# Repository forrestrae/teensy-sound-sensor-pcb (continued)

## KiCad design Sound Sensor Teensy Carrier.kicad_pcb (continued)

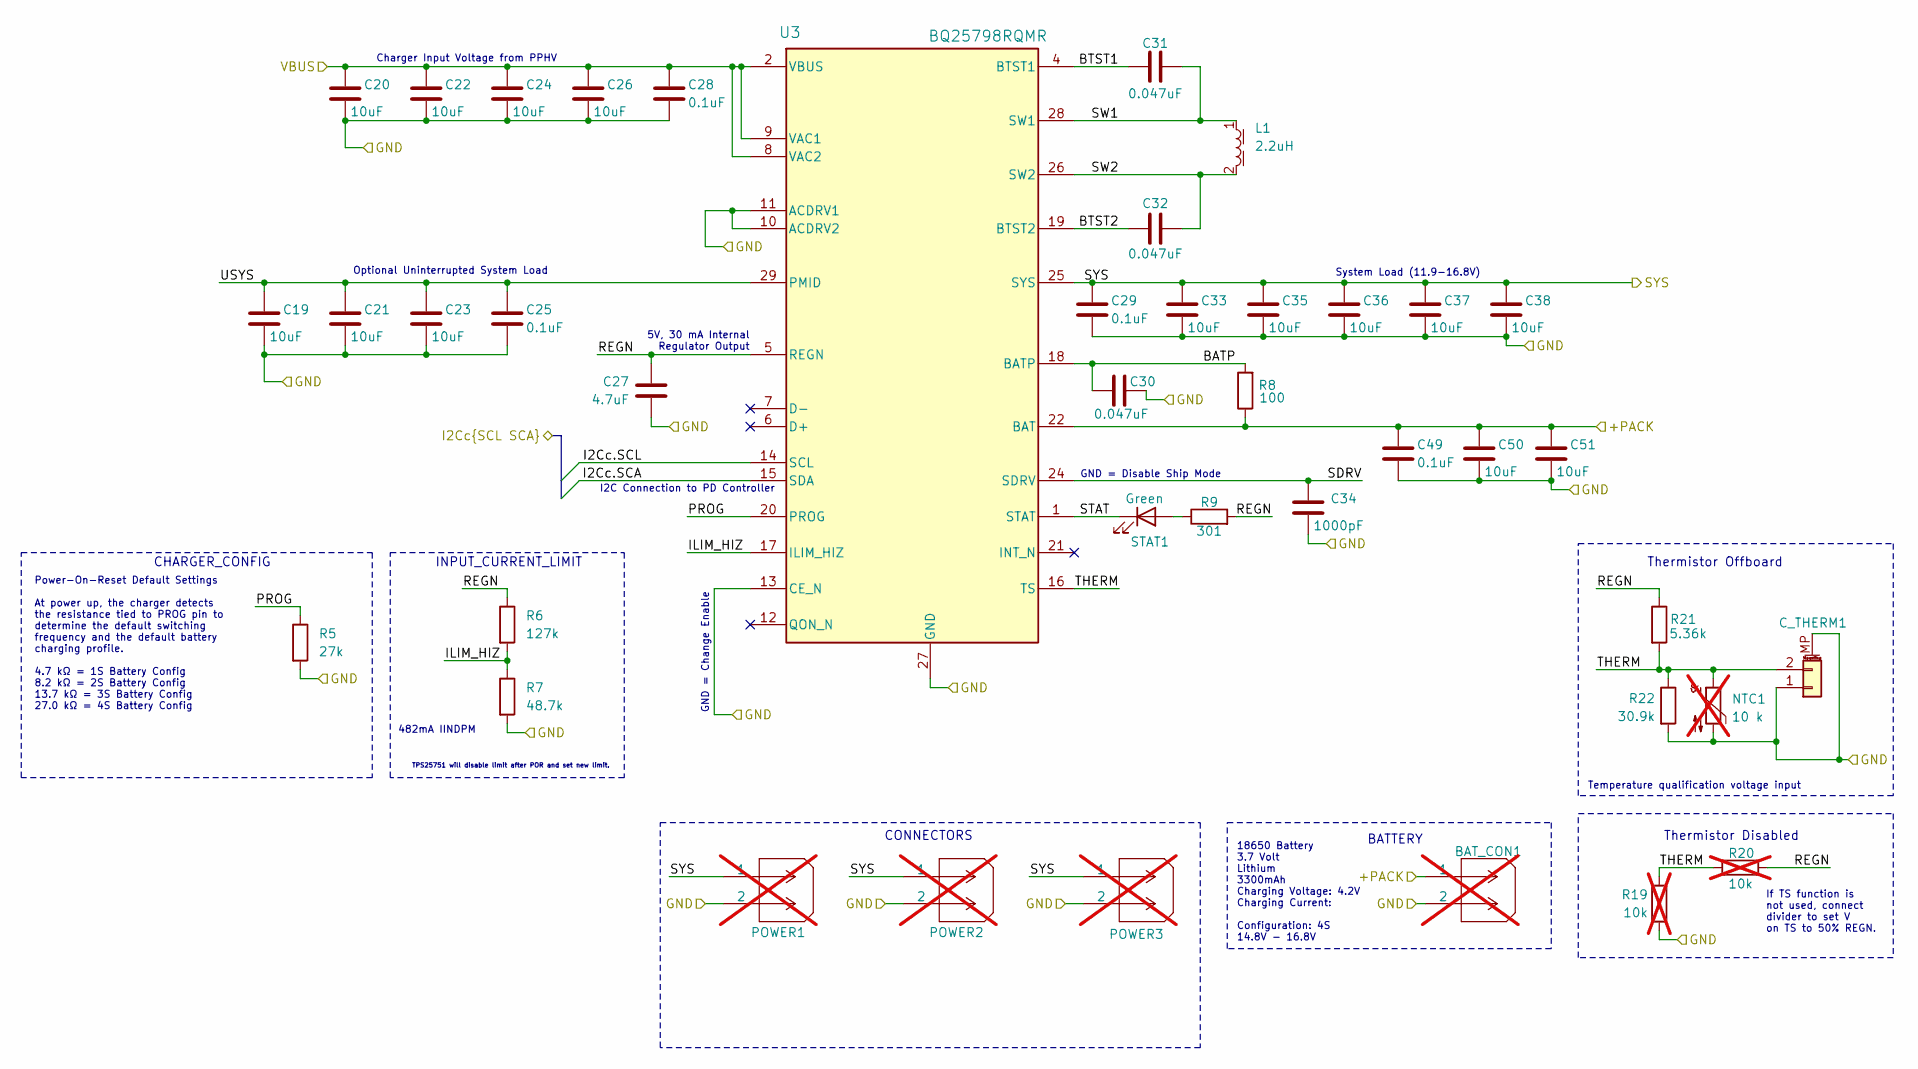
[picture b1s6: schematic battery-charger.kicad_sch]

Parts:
BAT_CON1: 218989-0210; CONN02_2189890210_MOL; MPN 218989-0210; Mouser SPN 538-218989-0210; not fitted
C19, C20, C21, C22, C23, C24, C26, C33, C35, C36, C37, C38, C50, C51: 10uF; C_0603_1608Metric; MPN GRM188R6YA106MA73D; Mouser SPN 81-GRM188R6YA106MA3D
C25, C28, C29, C49: 0.1uF; C_0603_1608Metric; MPN GCM188R71H104KA57J; Mouser SPN 81-GCM188R71H104KA7J
C27: 4.7uF; C_0603_1608Metric; MPN GRM188R6YA475KE15D; Mouser SPN 81-GRM188R6YA475KE5D
C30, C31, C32: 0.047uF; C_0603_1608Metric; MPN VJ0603Y473JXQPW1BC; Mouser SPN 77-VJ0603Y473JXQPBC
C34: 1000pF; C_0603_1608Metric; MPN GRM1885C1H102JA01J; Mouser SPN 81-GRM1885C1H102JA1J
C_THERM1: NTC_CHGR; Molex_Pico-Clasp_203558-0207_1x02-1MP_P1.00mm_Horizontal; MPN 203558-0207; Mouser SPN 538-203558-0207
L1: 2.2uH; L_Wurth_WE-LHMI-7030; MPN 74437346022; Mouser SPN 710-74437346022
NTC1: 10 k; PinHeader_1x02_P2.54mm_Vertical; MPN 103AT-2; Mouser SPN 954-103AT-2; not fitted
POWER1, POWER2, POWER3: 218989-0210; CONN02_2189890210_MOL; MPN 218989-0210; Mouser SPN 538-218989-0210; not fitted
R5: 27k; R_0603_1608Metric; MPN RCS060327K0FKEA; Mouser SPN 71-RCS060327K0FKEA
R6: 127k; R_0603_1608Metric; MPN CRCW0603127KFKEA; Mouser SPN 71-CRCW0603-127K-E3
R7: 48.7k; R_0603_1608Metric; MPN CRCW060348K7FKEA; Mouser SPN 71-CRCW0603-48.7K-E3
R8: 100; R_0603_1608Metric; MPN RCS0603100RFKEA; Mouser SPN 71-RCS0603100RFKEA
R9: 301; R_0603_1608Metric; MPN RCS0603301RFKEA; Mouser SPN 71-RCS0603301RFKEA
R19, R20: 10k; R_0603_1608Metric; MPN RCS060310K0FKEA; Mouser SPN 71-RCS060310K0FKEA; not fitted
R21: 5.36k; R_0603_1608Metric; MPN CRCW06035K36FKEA; Mouser SPN 71-CRCW0603-5.36K-E3
R22: 30.9k; R_0603_1608Metric; MPN CRCW060330K9FKEA; Mouser SPN 71-CRCW0603-30.9K-E3
STAT1: Green; LED_0805_2012Metric; MPN 150080GS75000; Mouser SPN 710-150080GS75000
U3: BQ25798RQMR; VQFN-HR-RQM-29; MPN BQ25798RQMR; Mouser SPN 595-BQ25798RQMR

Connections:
/Battery Charger/+PACK: BAT_CON1.1, C49.1, C50.1, C51.1, R8.1, U3.22 (BAT), U3.23 (BAT); also elsewhere on the board
/Battery Charger/BATP: C30.1, R8.2, U3.18 (BATP)
/Battery Charger/BTST1: C31.2, U3.4 (BTST1)
/Battery Charger/BTST2: C32.1, U3.19 (BTST2)
/Battery Charger/I2Cc.SCA: U3.15 (SDA); also elsewhere on the board
/Battery Charger/I2Cc.SCL: U3.14 (SCL); also elsewhere on the board
/Battery Charger/ILIM_HIZ: R6.2, R7.1, U3.17 (ILIM_HIZ)
/Battery Charger/PROG: R5.1, U3.20 (PROG)
/Battery Charger/REGN: C27.1, R6.1, R9.2, R20.2, R21.1, U3.5 (REGN)
/Battery Charger/SDRV: C34.1, U3.24 (SDRV)
/Battery Charger/STAT: STAT1.1 (K), U3.1 (STAT)
/Battery Charger/SW1: C31.1, L1.1, U3.28 (SW1)
/Battery Charger/SW2: C32.2, L1.2, U3.26 (SW2)
/Battery Charger/SYS: C29.1, C33.1, C35.1, C36.1, C37.1, C38.1, POWER1.1, POWER2.1, POWER3.1, U3.25 (SYS); also elsewhere on the board
/Battery Charger/THERM: C_THERM1.2, NTC1.1, R19.1, R20.1, R21.2, R22.1, U3.16 (TS)
/Battery Charger/USYS: C19.1, C21.1, C23.1, C25.1, U3.29 (PMID)
/GND: BAT_CON1.2, C19.2, C20.2, C21.2, C22.2, C23.2, C24.2, C25.2, C26.2, C27.2, C28.2, C29.2, C30.2, C33.2, C34.2, C35.2, C36.2, C37.2, C38.2, C49.2, C50.2, C51.2, C_THERM1.1, C_THERM1.MP (MountPin), NTC1.2, POWER1.2, POWER2.2, POWER3.2, R5.2, R7.2, R19.2, R22.2, U3.10 (ACDRV2), U3.11 (ACDRV1), U3.13 (CE_N), U3.27 (GND); also elsewhere on the board
/PPHV: C20.1, C22.1, C24.1, C26.1, C28.1, U3.2 (VBUS), U3.3 (VBUS), U3.8 (VAC2), U3.9 (VAC1); also elsewhere on the board
unnamed: R9.1, STAT1.2 (A)

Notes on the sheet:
Optional Uninterrupted System Load
INPUT_CURRENT_LIMIT
18650 Battery 3.7 Volt Lithium 3300mAh Charging Voltage: 4.2V Charging Current: Configuration: 4S 14.8V - 16.8V
System Load (11.9-16.8V)
CHARGER_CONFIG
Thermistor Offboard
5V, 30 mA Internal Regulator Output
I2C Connection to PD Controller
If TS function is not used, connect divider to set V on TS to 50% REGN.
GND = Disable Ship Mode
Charger Input Voltage from PPHV
TPS25751 will disable limit after POR and set new limit.
GND = Change Enable
Thermistor Disabled
Power-On-Reset Default Settings At power up, the charger detects the resistance tied to PROG pin to determine the default switching frequency and the default battery charging profile. 4.7 kΩ = 1S Battery Config 8.2 kΩ = 2S Battery Config 13.7 kΩ = 3S Battery Config 27.0 kΩ = 4S Battery Config
482mA IINDPM
Temperature qualification voltage input
CONNECTORS
BATTERY

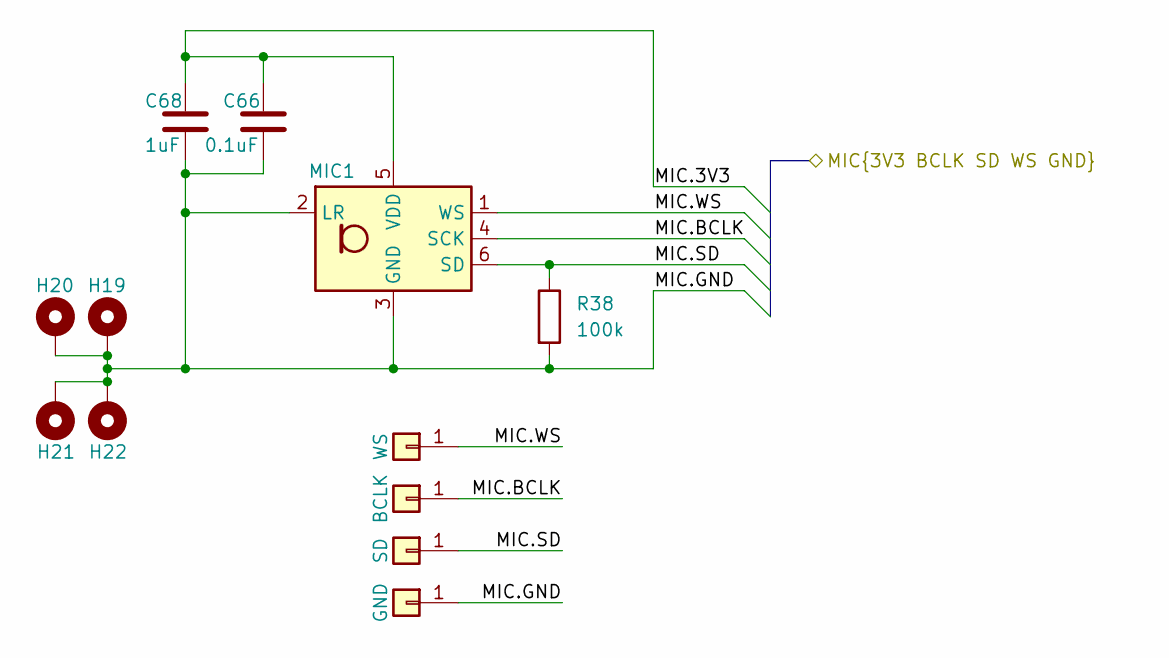
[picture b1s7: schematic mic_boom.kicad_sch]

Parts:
C66: 0.1uF; C_0603_1608Metric; MPN GCM188R71H104KA57J; Mouser SPN 81-GCM188R71H104KA7J
C68: 1uF; C_0603_1608Metric; MPN 06035C105KAT2A; Farnell SPN 4155078
H19, H20, H21, H22: MountingHole_Pad; MountingHole_2.2mm_M2_Pad
H35: WS; SolderWirePad_1x01_SMD_1x2mm
H36: BCLK; SolderWirePad_1x01_SMD_1x2mm
H37: SD; SolderWirePad_1x01_SMD_1x2mm
H38: GND; SolderWirePad_1x01_SMD_1x2mm
MIC1: ICS-43434; InvenSense_ICS-43434-6_3.5x2.65mm; MPN ICS-43434; Mouser SPN 410-ICS-43434
R38: 100k; R_0603_1608Metric; MPN RCS0603100KFKEA; Mouser SPN 71-RCS0603100KFKEA

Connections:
/Mic Boom/MIC.3V3: C66.1, C68.1, MIC1.5 (VDD); also elsewhere on the board
/Mic Boom/MIC.BCLK: H36.1, MIC1.4 (SCK); also elsewhere on the board
/Mic Boom/MIC.GND: C66.2, C68.2, H19.1, H20.1, H21.1, H22.1, H38.1, MIC1.2 (LR), MIC1.3 (GND), R38.2; also elsewhere on the board
/Mic Boom/MIC.SD: H37.1, MIC1.6 (SD), R38.1; also elsewhere on the board
/Mic Boom/MIC.WS: H35.1, MIC1.1 (WS); also elsewhere on the board

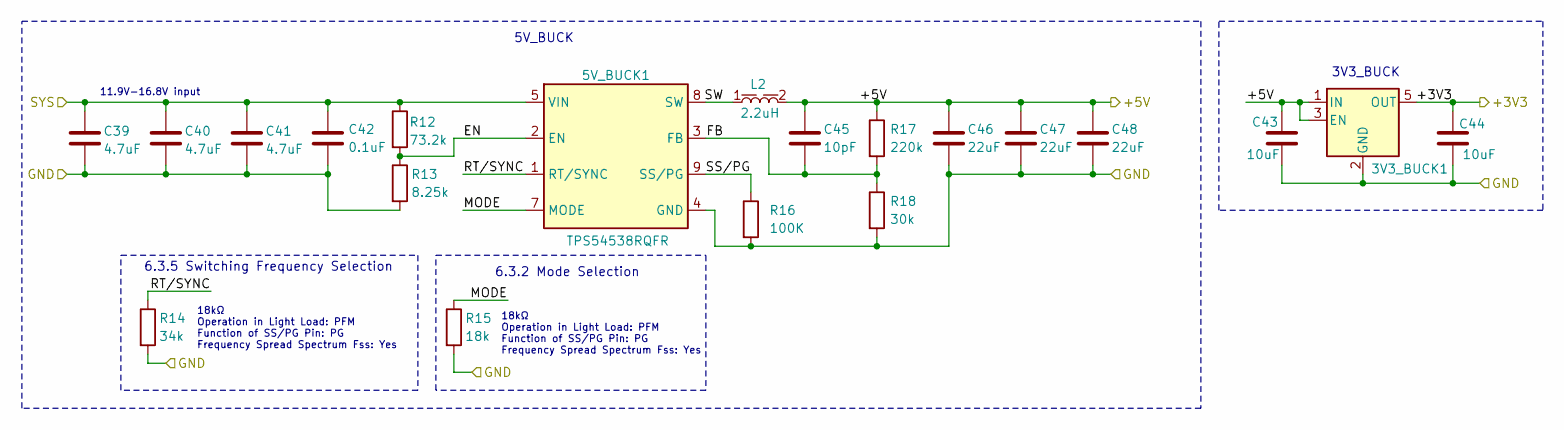
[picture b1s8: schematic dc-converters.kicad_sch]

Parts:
3V3_BUCK1: 3.3V; SOT-23-5; MPN TLV75533PDBVR; Mouser SPN 595-TLV75533PDBVR
5V_BUCK1: TPS54538RQFR; VQFN-HR-RQF-9; MPN TPS54538RQFR; Mouser SPN 595-TPS54538RQFR
C39, C40, C41: 4.7uF; C_0603_1608Metric; MPN GRM188R6YA475KE15D; Mouser SPN 81-GRM188R6YA475KE5D
C42: 0.1uF; C_0603_1608Metric; MPN GCM188R71H104KA57J; Mouser SPN 81-GCM188R71H104KA7J
C43, C44: 10uF; C_0603_1608Metric; MPN GRM188R6YA106MA73D; Mouser SPN 81-GRM188R6YA106MA3D
C45: 10pF; C_0603_1608Metric; MPN 06033A100FAT2A; Mouser SPN 581-06033A100FAT2A
C46, C47, C48: 22uF; C_0603_1608Metric; MPN GRM188R61A226ME15J; Mouser SPN 81-GRM188R61A226ME5J
L2: 2.2uH; L_Wurth_WE-LHMI-7030; MPN 74437346022; Mouser SPN 710-74437346022
R12: 73.2k; R_0603_1608Metric; MPN CRCW060373K2FKEA; Mouser SPN 71-CRCW0603-73.2K-E3
R13: 8.25k; R_0603_1608Metric; MPN CRCW06038K25FKEA; Mouser SPN 71-CRCW0603-8.25K-E3
R14: 34k; R_0603_1608Metric; MPN CRCW060334K0FKEA; Mouser SPN 71-CRCW0603-34K-E3
R15: 18k; R_0603_1608Metric; MPN CRCW060318K0FKEA; Mouser SPN 71-CRCW0603-18K-E3
R16: 100K; R_0603_1608Metric; MPN RCS0603100KFKEA; Mouser SPN 71-RCS0603100KFKEA
R17: 220k; R_0603_1608Metric; MPN RCS0603220KFKEA; Mouser SPN 71-RCS0603220KFKEA
R18: 30k; R_0603_1608Metric; MPN CRCW060330K0FKEA; Mouser SPN 71-CRCW0603-30K-E3

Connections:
/+3V3: 3V3_BUCK1.5 (OUT), C44.1; also elsewhere on the board
/+5V: 3V3_BUCK1.1 (IN), 3V3_BUCK1.3 (EN), C43.1, C45.1, C46.1, C47.1, C48.1, L2.2, R17.1; also elsewhere on the board
/Battery Charger/SYS: 5V_BUCK1.5 (VIN), 5V_BUCK1.6 (VIN), C39.1, C40.1, C41.1, C42.1, R12.1; also elsewhere on the board
/DC Converters/EN: 5V_BUCK1.2 (EN), R12.2, R13.1
/DC Converters/FB: 5V_BUCK1.3 (FB), C45.2, R17.2, R18.1
/DC Converters/MODE: 5V_BUCK1.7 (MODE), R15.1
/DC Converters/SS/PG: 5V_BUCK1.9 (SS/PG), R16.1
/DC Converters/SW: 5V_BUCK1.8 (SW), L2.1
/GND: 3V3_BUCK1.2 (GND), 5V_BUCK1.4 (GND), C39.2, C40.2, C41.2, C42.2, C43.2, C44.2, C46.2, C47.2, C48.2, R13.2, R14.2, R15.2, R16.2, R18.2; also elsewhere on the board

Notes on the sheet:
18kΩ Operation in Light Load: PFM Function of SS/PG Pin: PG Frequency Spread Spectrum Fss: Yes
6.3.2 Mode Selection
3V3_BUCK
11.9V-16.8V input
6.3.5 Switching Frequency Selection
5V_BUCK

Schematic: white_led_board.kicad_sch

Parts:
C67, C76: 22uF; C_0805_2012Metric; MPN C2012X5R1V226M125AC; DigiKey SPN 445-14428-2-ND
C69, C72: 1uF; C_0603_1608Metric; MPN 06035C105KAT2A; Mouser SPN 581-06035C105KAT2A
C70, C71, C77: 0.1uF; C_0603_1608Metric; MPN GCM188R71H104KA57J; Mouser SPN 81-GCM188R71H104KA7J
C74: 1nF; C_0603_1608Metric; MPN GRM1885C1H102JA01J; Mouser SPN 81-GRM1885C1H102JA1J
C_{FLT}73: 1nF; C_0603_1608Metric; MPN GRM1885C1H102JA01J; Mouser SPN 81-GRM1885C1H102JA1J
C_{SNS}75: 1uF; C_0603_1608Metric; MPN 06035C105KAT2A; Mouser SPN 581-06035C105KAT2A
D3: 700mV; TO-277A; MPN STPST10H100SFY; DigiKey SPN 497-STPST10H100SFYTR-ND
D4, D5, D6, D7, D8, D9, D10, D11, D12, D13, D14, D15, D16, D17, D18, D19, D20, D21, D22, D23, D24, D25, D26, D27, D28, D29, D30, D31, D32, D33, D34, D35, D36, D37, D38, D39, D40, D41, D42, D43, D44, D45, D46, D47, D48, D49, D50, D51: 158302250; D_Wurth_WL-SWTP_3022; MPN 158302250; Mouser SPN 710-158302250
L4: 10uH; L_Wurth_WE-HCI-7050; Part Number 744314101; Farnell UK SPN 1890614
R40: 100; R_0603_1608Metric; MPN RCS0603100RFKEA; Mouser SPN 71-RCS0603100RFKEA
R41: 40.2k; R_0603_1608Metric; MPN RCS060340K2FKEA; DigiKey SPN 541-10468-2-ND
R44: 1.1M; R_0603_1608Metric; MPN CRCW06031M10FKEA; DigiKey SPN 541-5250-2-ND
R45: 48.7k; R_0603_1608Metric; MPN CRCW060348K7FKEA; Mouser SPN 71-CRCW0603-48.7K-E3
R46: 18k; R_0603_1608Metric; MPN CRCW060318K0FKEA; Mouser SPN 71-CRCW0603-18K-E3
R_{FLT}39: 100; R_0603_1608Metric; MPN RCS0603100RFKEA; Mouser SPN 71-RCS0603100RFKEA
R_{FSET}42: 27k; R_0603_1608Metric; MPN RCS060327K0FKEA; Mouser SPN 71-RCS060327K0FKEA; not fitted
R_{SNS}43: 560m; R_0805_2012Metric; MPN ERJ-6DQFR56V; Mouser SPN 667-ERJ-6DQFR56V
U5: TPS923652DRRR; Texas_DRR0012C_WSON-12-DRR_0.8mm; MPN TPS923652DRRR; DigiKey SPN 296-TPS923652DRRRTR-ND

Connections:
/White LED Board/+VLED: C76.1, C77.1, C_{SNS}75.1, D4.2 (+), D12.2 (+), D20.2 (+), D28.2 (+), D36.2 (+), D44.2 (+), R44.1, R_{FLT}39.2, R_{SNS}43.2
/White LED Board/ADIM: U5.3 (ADIM); also elsewhere on the board
/White LED Board/COMP: R40.1, U5.8 (COMP)
/White LED Board/CSN: C_{FLT}73.2, R_{FLT}39.1, U5.10 (CSN)
/White LED Board/CSP: C_{FLT}73.1, C_{SNS}75.2, D3.3 (K), R_{SNS}43.1, U5.11 (CSP)
/White LED Board/FSET: R46.1, R_{FSET}42.1, U5.7 (FSET)
/White LED Board/GND: C67.1, C69.2, C70.2, C71.2, C72.2, C74.2, C76.2, C77.2, D4.3 (PAD), D5.3 (PAD), D6.3 (PAD), D7.3 (PAD), D8.3 (PAD), D9.3 (PAD), D10.3 (PAD), D11.1 (-), D11.3 (PAD), D12.3 (PAD), D13.3 (PAD), D14.3 (PAD), D15.3 (PAD), D16.3 (PAD), D17.3 (PAD), D18.3 (PAD), D19.1 (-), D19.3 (PAD), D20.3 (PAD), D21.3 (PAD), D22.3 (PAD), D23.3 (PAD), D24.3 (PAD), D25.3 (PAD), D26.3 (PAD), D27.1 (-), D27.3 (PAD), D28.3 (PAD), D29.3 (PAD), D30.3 (PAD), D31.3 (PAD), D32.3 (PAD), D33.3 (PAD), D34.3 (PAD), D35.1 (-), D35.3 (PAD), D36.3 (PAD), D37.3 (PAD), D38.3 (PAD), D39.3 (PAD), D40.3 (PAD), D41.3 (PAD), D42.3 (PAD), D43.1 (-), D43.3 (PAD), D44.3 (PAD), D45.3 (PAD), D46.3 (PAD), D47.3 (PAD), D48.3 (PAD), D49.3 (PAD), D50.3 (PAD), D51.1 (-), D51.3 (PAD), R41.2, R45.2, U5.5 (nFault), U5.13 (GND), U5.14 (GND), U5.15 (GND), U5.16 (GND), U5.17 (GND); also elsewhere on the board
/White LED Board/OVP: R44.2, R45.1, U5.9 (OVP)
/White LED Board/PWM: U5.4 (PWM); also elsewhere on the board
/White LED Board/SW: D3.1 (A), D3.2 (A), L4.2, U5.12 (SW)
/White LED Board/TEMP: R41.1, U5.6 (TEMP)
/White LED Board/VCC: C72.1, U5.2 (VCC)
/White LED Board/VIN: C67.2, C69.1, C70.1, C71.1, L4.1, U5.1 (VIN); also elsewhere on the board
unnamed: C74.1, R40.2
unnamed: D4.1 (-), D5.2 (+)
unnamed: D5.1 (-), D6.2 (+)
unnamed: D6.1 (-), D7.2 (+)
unnamed: D7.1 (-), D8.2 (+)
unnamed: D8.1 (-), D9.2 (+)
unnamed: D9.1 (-), D10.2 (+)
unnamed: D10.1 (-), D11.2 (+)
unnamed: D12.1 (-), D13.2 (+)
unnamed: D13.1 (-), D14.2 (+)
unnamed: D14.1 (-), D15.2 (+)
unnamed: D15.1 (-), D16.2 (+)
unnamed: D16.1 (-), D17.2 (+)
unnamed: D17.1 (-), D18.2 (+)
unnamed: D18.1 (-), D19.2 (+)
unnamed: D20.1 (-), D21.2 (+)
unnamed: D21.1 (-), D22.2 (+)
unnamed: D22.1 (-), D23.2 (+)
unnamed: D23.1 (-), D24.2 (+)
unnamed: D24.1 (-), D25.2 (+)
unnamed: D25.1 (-), D26.2 (+)
unnamed: D26.1 (-), D27.2 (+)
unnamed: D28.1 (-), D29.2 (+)
unnamed: D29.1 (-), D30.2 (+)
unnamed: D30.1 (-), D31.2 (+)
unnamed: D31.1 (-), D32.2 (+)
unnamed: D32.1 (-), D33.2 (+)
unnamed: D33.1 (-), D34.2 (+)
unnamed: D34.1 (-), D35.2 (+)
unnamed: D36.1 (-), D37.2 (+)
unnamed: D37.1 (-), D38.2 (+)
unnamed: D38.1 (-), D39.2 (+)
unnamed: D39.1 (-), D40.2 (+)
unnamed: D40.1 (-), D41.2 (+)
unnamed: D41.1 (-), D42.2 (+)
unnamed: D42.1 (-), D43.2 (+)
unnamed: D44.1 (-), D45.2 (+)
unnamed: D45.1 (-), D46.2 (+)
unnamed: D46.1 (-), D47.2 (+)
unnamed: D47.1 (-), D48.2 (+)
unnamed: D48.1 (-), D49.2 (+)
unnamed: D49.1 (-), D50.2 (+)
unnamed: D50.1 (-), D51.2 (+)
unnamed: R46.2, R_{FSET}42.2

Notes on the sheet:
7.3.8 Thermal Foldback
Switching Freq Resistor 0.1 MHz = 160 kΩ 0.2 MHz = 95 kΩ 0.3 MHz = 67 kΩ 0.4 MHz = 52 kΩ 0.5 MHz = 43.5 kΩ 0.6 MHz = 35 kΩ 0.8 MHz = 27 kΩ 1.0 MHz = 21 kΩ 1.2 MHz = 18 kΩ 1.5 MHz = 14 kΩ 1.8 MHz = 11 kΩ 2.2 MHz = 9.2 kΩ

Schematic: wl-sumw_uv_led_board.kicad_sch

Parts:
C73, C79: 0.1uF; C_0603_1608Metric; MPN GCM188R71H104KA57J; Mouser SPN 81-GCM188R71H104KA7J
C75, C78: 10uF; C_0603_1608Metric; MPN GRM188R6YA106MA73D; Mouser SPN 81-GRM188R6YA106MA3D
D52, D53: 3535 UV-A; D_Wurth_WL-SUMW_3535_153353XXAA350; MPN 15335337AA350; Mouser SPN 710-15335337AA350
H28: PWM; SolderWirePad_1x01_SMD_1.5x3mm; not fitted
H29: VIN; SolderWirePad_1x01_SMD_2x4mm; not fitted
H30: GND; SolderWirePad_1x01_SMD_2x4mm; not fitted
H31, H32, H33, H34: MountingHole_Pad; MountingHole_2.2mm_M2_Pad
L3: 8.2uH; L_Wurth_WE-MAIA-4030; MPN 78438357082; DigiKey SPN 732-11745-2-ND
R_{fb}1: 0; R_0603_1608Metric; MPN RCC06030000Z0EA; Mouser SPN 71-RCC06030000Z0EA
R_{sns}2: 0.143; R_0603_1608Metric; MPN SR731JTTDR143F; DigiKey SPN 2019-SR731JTTDR143FTR-ND
U6: TPS92200D2DDCR; SOT-23-6; MPN TPS92200D2DDCR; DigiKey SPN 296-TPS92200D2DDCRTR-ND

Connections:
/WL-SUMW UV LED Board/BOOT: C73.2, U6.6 (BOOT)
/WL-SUMW UV LED Board/FB: R_{fb}1.1, U6.1 (FB)
/WL-SUMW UV LED Board/GND: C75.2, C78.2, C79.2, D52.3 (THERM), D53.3 (THERM), H31.1, H32.1, H33.1, H34.1, R_{sns}2.2, U6.3 (GND); also elsewhere on the board
/WL-SUMW UV LED Board/PWM: H28.1, U6.2 (DIM); also elsewhere on the board
/WL-SUMW UV LED Board/SENSE: D53.1 (C), R_{fb}1.2, R_{sns}2.1
/WL-SUMW UV LED Board/SW: C73.1, L3.1, U6.5 (SW)
/WL-SUMW UV LED Board/VIN: C78.1, C79.1, U6.4 (VIN); also elsewhere on the board
/WL-SUMW UV LED Board/VOUT: C75.1, D52.2 (A), L3.2
unnamed: D52.1 (C), D53.2 (A)

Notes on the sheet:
7.3.2 Setting LED Current: R_{SNS} = V_{FB_REF} / I_{LED} V_{FB_REF} is fixed at 0.099 V, I_{LED} = 0.700 A 0.099 / 0.700 = 141 mΩ (next common size = 143 mΩ)
Used to measure the loop response
Passthrough Connection

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
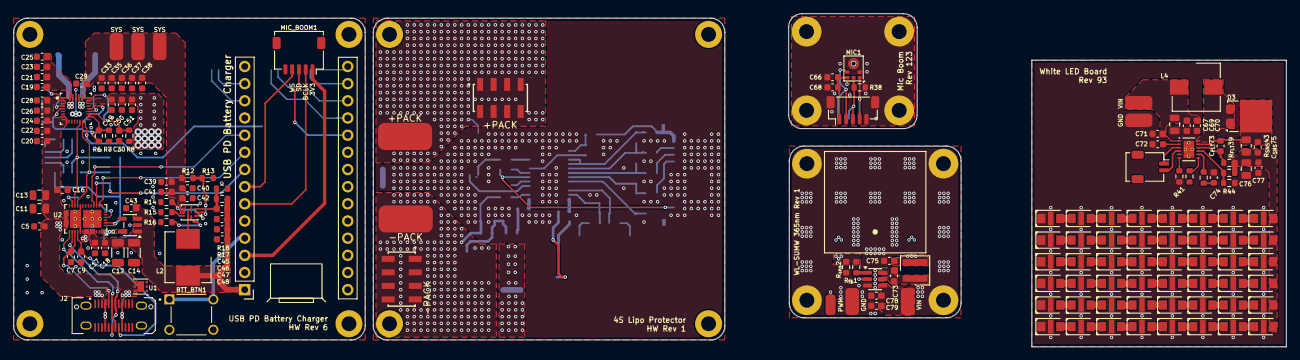
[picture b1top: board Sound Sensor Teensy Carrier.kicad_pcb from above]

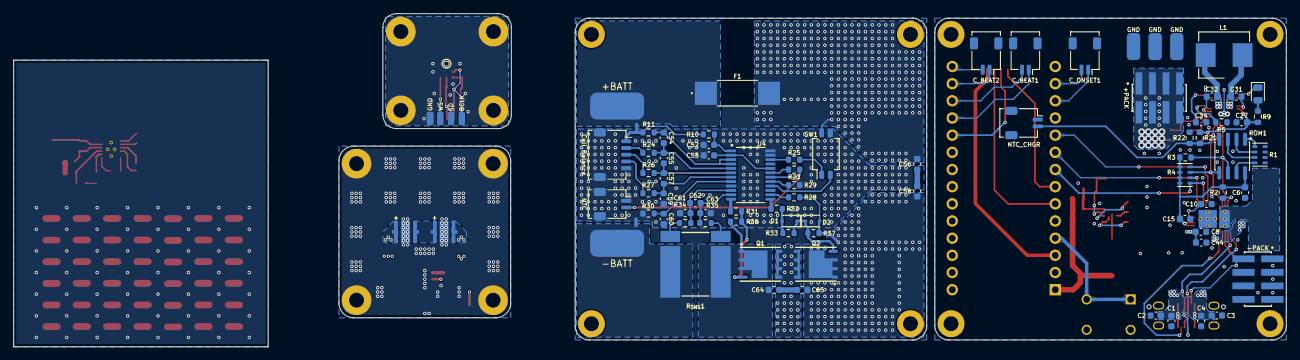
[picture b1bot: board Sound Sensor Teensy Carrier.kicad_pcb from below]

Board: 4 copper layers, 188.3 x 49.3 mm, 257 parts (84 on the bottom side), 160 nets.

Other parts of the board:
B1, B2, B3, B4, B6: Board

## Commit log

2026-04-01 Update `.gitignore` with additional project-specific files
2026-04-01 Add initial project documentation in `README.md` outlining features, architecture, and usage
2026-04-01 Initial commit of design.
2026-04-01 Add `separate.zsh` script for PCB component extraction automation
2026-04-01 Update `.gitignore` to exclude `.DS_Store` files
2026-04-23 Remove Incorrect link to a firmware repository that doesn't exist (yet).
